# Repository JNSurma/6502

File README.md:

# 6502_sbc
My 6502 Home-brew Computer

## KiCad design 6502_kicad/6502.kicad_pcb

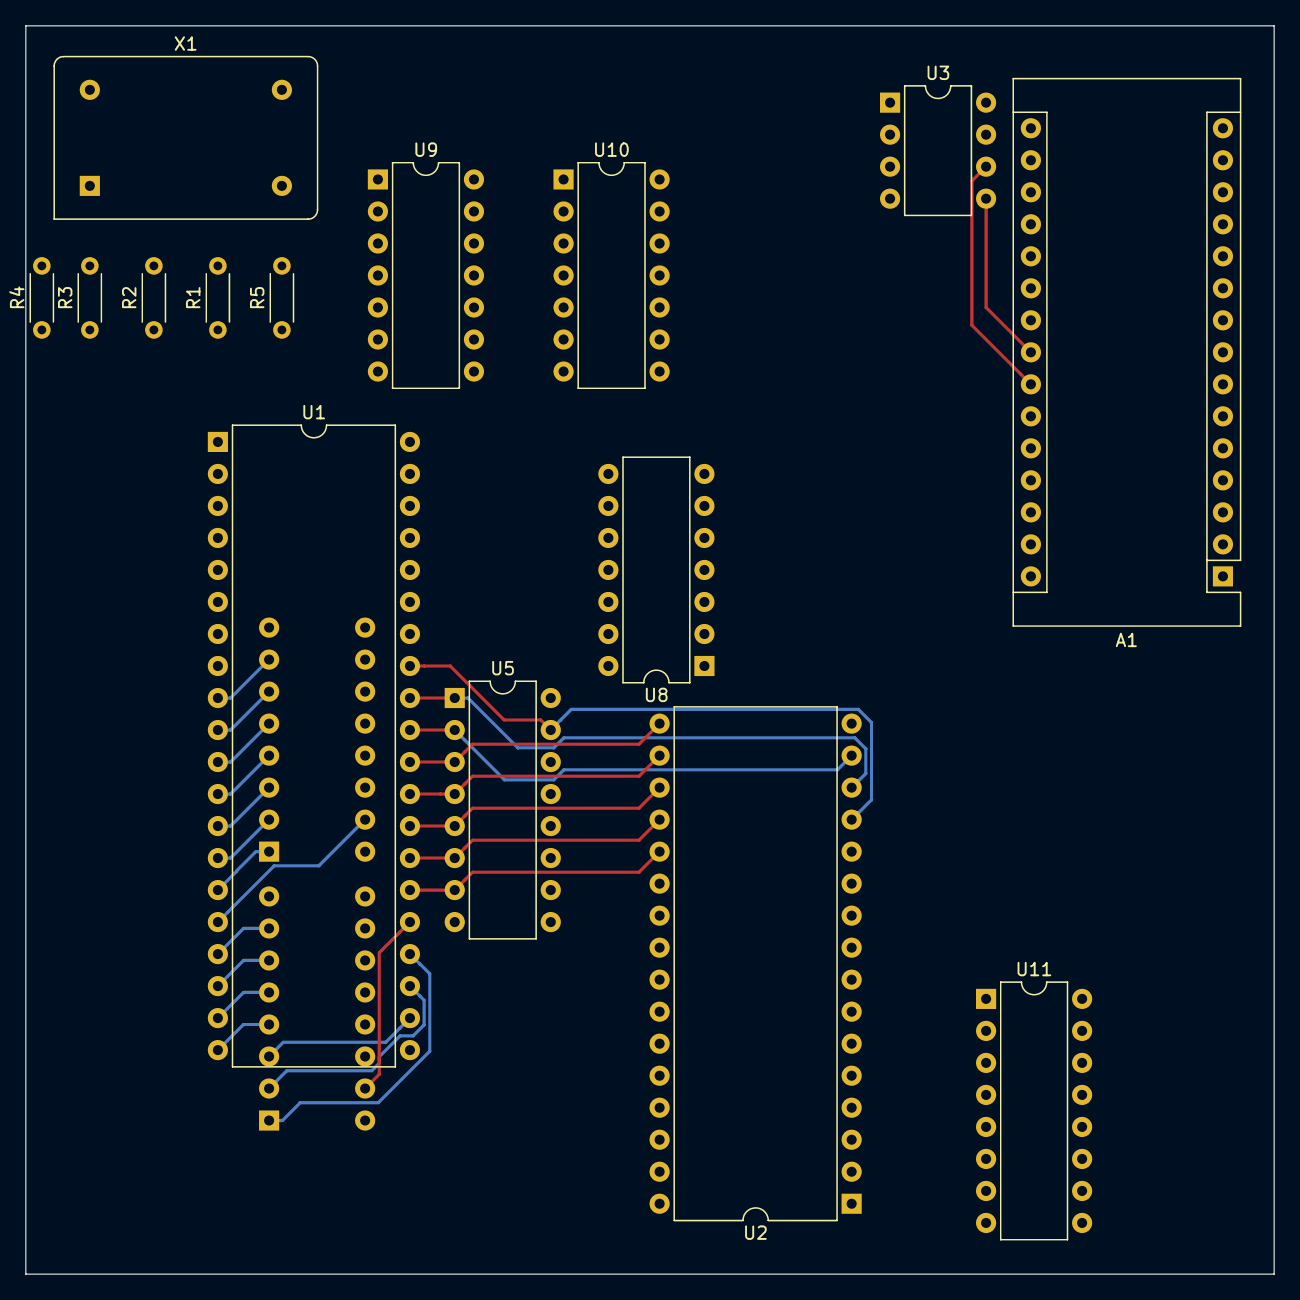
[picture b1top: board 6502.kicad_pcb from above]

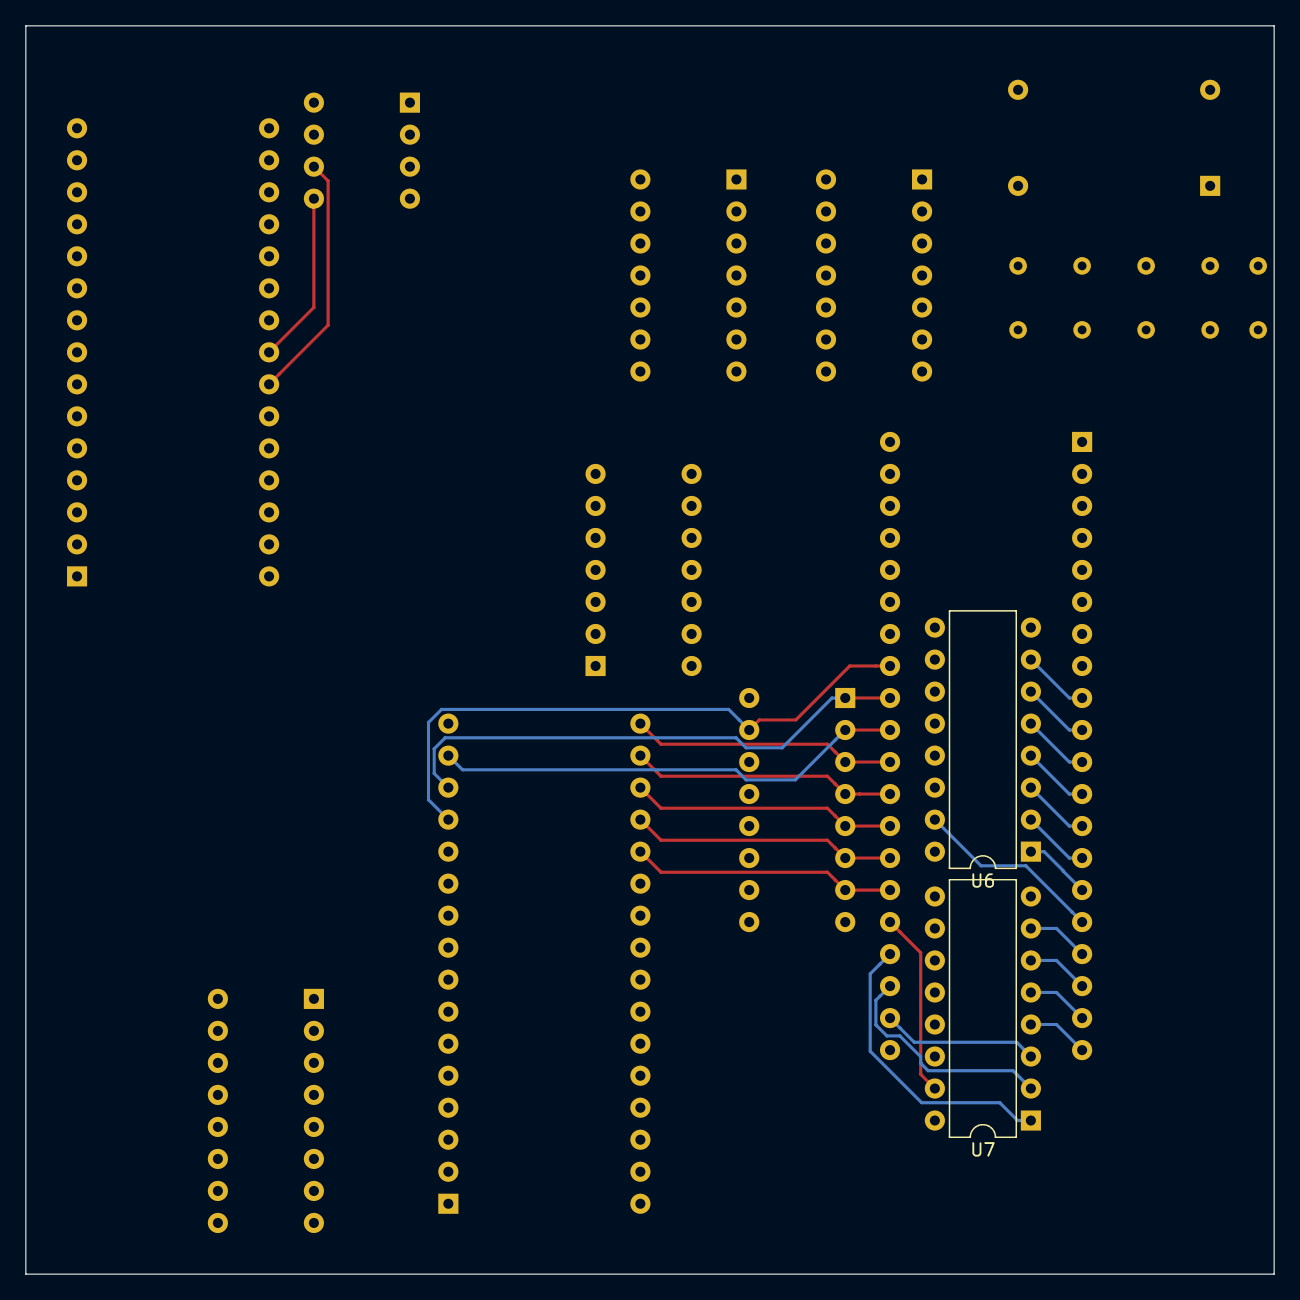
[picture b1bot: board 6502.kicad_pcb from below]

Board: 2 copper layers, 99.1 x 99.1 mm, 17 parts (2 on the bottom side), 46 nets.

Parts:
A1: Arduino_Nano_v2.x; Arduino_Nano
R1, R2, R3, R4, R5: 3.3K; R_Axial_DIN0204_L3.6mm_D1.6mm_P5.08mm_Horizontal
U1: WD65C02; DIP-40_W15.24mm
U2: 628128; DIP-32_W15.24mm
U3: 24C256; DIP-8_W7.62mm
U5, U6, U7: 74HCT595; DIP-16_W7.62mm
U8: 74LS30; DIP-14_W7.62mm
U9: 74LS08; DIP-14_W7.62mm
U10: 74LS04; DIP-14_W7.62mm
U11: 74LS138; DIP-16_W7.62mm
X1: CXO_DIP14; Oscillator_DIP-14

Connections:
+5V: A1.30, R1.2, R2.2, R3.2, R4.2, R5.2, U1.8, U1.38, U2.32, U3.7, U3.8, U5.16, U6.16, U7.16, U11.16, X1.14
/Bus_Enable: A1.9, R5.1, U1.36, U5.13, U6.13, U7.13
/CS_IO: U10.6, U11.6
/a0: U1.9, U2.12, U6.7
/a1: U1.10, U2.11, U6.6
/a2: U1.11, U2.10, U6.5
/a3: U1.12, U2.9, U6.4
/a4: U1.13, U2.8, U6.3, U11.1
/a5: U1.14, U2.7, U6.2, U11.2
/a6: U1.15, U2.6, U6.1, U11.3
/a7: U1.16, U2.5, U6.15, U10.1
/a8: U1.17, U2.27, U7.7, U8.12
/a9: U1.18, U2.26, U7.6, U8.11
/a10: U1.19, U2.23, U7.5, U8.6
/a11: U1.20, U2.25, U7.4, U8.5
/a12: U1.22, U2.4, U7.3, U8.4
/a13: U1.23, U2.28, U7.2, U8.3
/a14: U1.24, U2.3, U7.1, U8.2
/a15: U1.25, U2.31, U7.15, U8.1
/d0: U1.33, U2.13, U5.15
/d1: U1.32, U2.14, U5.1
/d2: U1.31, U2.15, U5.2
/d3: U1.30, U2.17, U5.3
/d4: U1.29, U2.18, U5.4
/d5: U1.28, U2.19, U5.5
/d6: U1.27, U2.20, U5.6
/d7: U1.26, U2.21, U5.7
/phi2out: U1.39, U2.30
/~CS_RAM: U2.22, U2.24, U9.3, U10.5
GND: A1.4, A1.29, U1.21, U2.2, U2.16, U3.1, U3.2, U3.3, U3.4, U5.8, U6.8, U7.8, U11.4, U11.5, U11.8, X1.7
unnamed: A1.5, U7.14
unnamed: A1.6, U5.11, U6.11, U7.11
unnamed: A1.7, U5.12, U6.12, U7.12
unnamed: A1.8, U1.34, U2.29
unnamed: A1.23, U3.5
unnamed: A1.24, U3.6
unnamed: R1.1, U1.40
unnamed: R2.1, U1.2
unnamed: R3.1, U1.4
unnamed: R4.1, U1.6
unnamed: U1.37, X1.8
unnamed: U5.14, U6.9
unnamed: U6.14, U7.9
unnamed: U9.2, U10.2
unnamed: U8.8, U10.3
unnamed: U9.1, U10.4

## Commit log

2021-01-01 Update .gitignore
    Add backup files to .gitignore:
    *.bak
    *~
2021-01-01 Re-upload
    Re-upload without other project's files mixed in.
2021-01-03 Addressing working, Data_LCS working. Needed PHI2 on the 138. Need to update schematic.
2021-01-03 Forgot to add new files...
2021-01-03 Consolidated old address schemes to one file.
2021-01-03 Just testing git.
2021-01-04 Update addr and test communication to 65c22. - addr.txt refected incorrect use of PHI2 because LCD needs it for operation, but other chips don't(?), such as the 65c22, which failed to run with PHI2 o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
